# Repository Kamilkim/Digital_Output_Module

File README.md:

# Digital_Output_Module
Digital output to extend number of output of PLC Siemens

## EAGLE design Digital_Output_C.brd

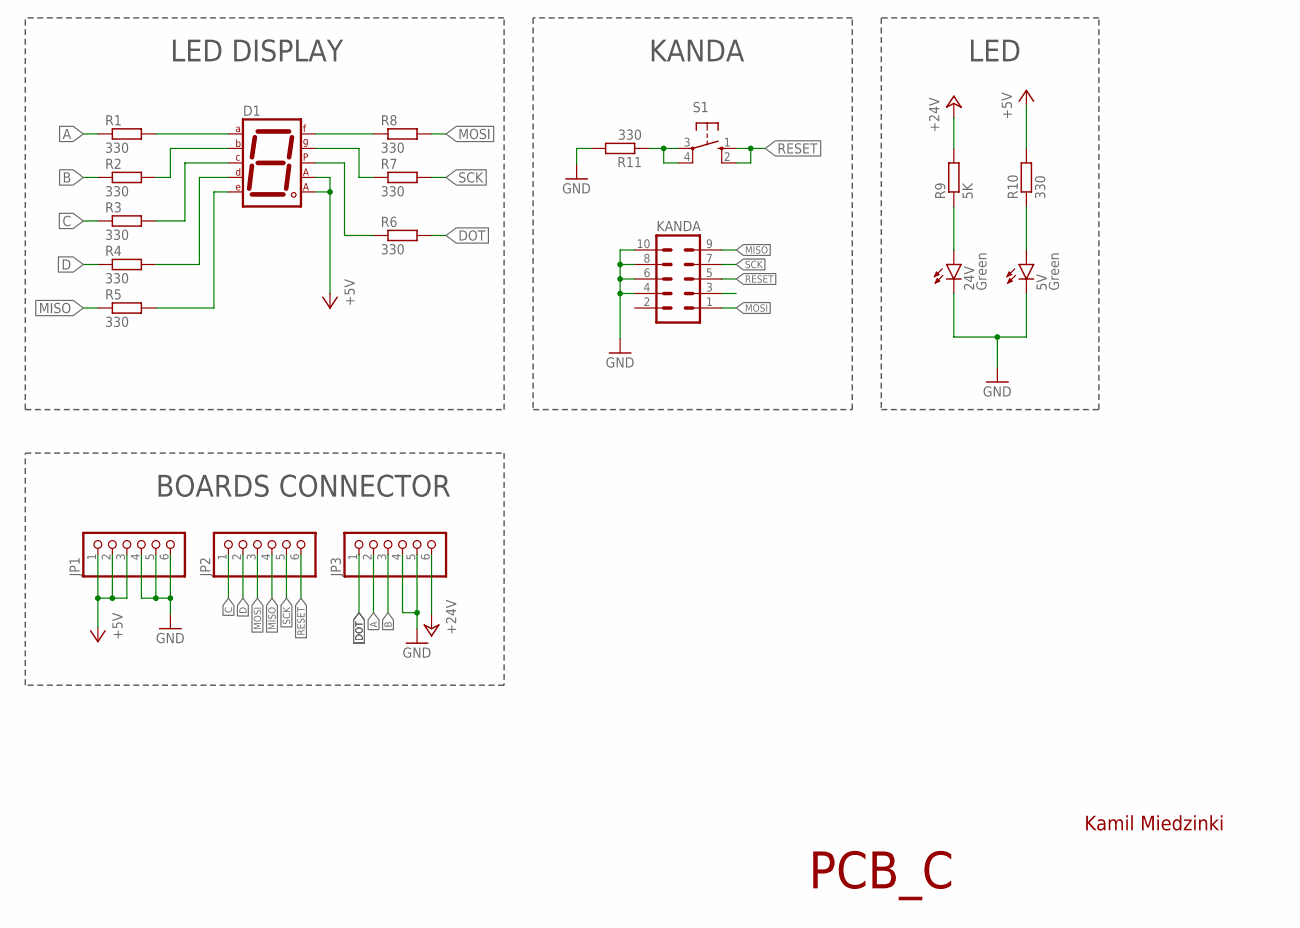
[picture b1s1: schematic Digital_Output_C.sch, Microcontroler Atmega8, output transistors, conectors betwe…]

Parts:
5V, 24V: Green; LED5MM
D1: 7SEG-CA; 7SEG-13
JP1, JP2, JP3: PINHD-1X6"; 1X06H
KANDA: ML10
R1, R2, R3, R4, R5, R6, R7, R8, R11: 330; R0805
R9: 5K; 0207/7
R10: 330; 0207/7
S1: 10-XX; B3F-10XX

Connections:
+5V: D1.3 (CA1), D1.8 (CA2), JP1.1, JP1.2, JP1.3, R10.2
+24V: JP3.6, R9.2
A: JP3.2, R1.1
B: JP3.3, R2.1
C: JP2.1, R3.1
D: JP2.2, R4.1
DOT: JP3.1, R6.2
GND: 5V.K (C), 24V.K (C), JP1.4, JP1.5, JP1.6, JP3.4, JP3.5, KANDA.4, KANDA.6, KANDA.8, KANDA.10, R11.2
MISO: JP2.4, KANDA.9, R5.1
MOSI: JP2.3, KANDA.1, R8.2
unnamed: R11.1, S1.3, S1.4 (P1)
unnamed: D1.7 (A), R1.2
unnamed: D1.6 (B), R2.2
unnamed: D1.4 (C), R3.2
unnamed: D1.2 (D), R4.2
unnamed: D1.1 (E), R5.2
unnamed: D1.9 (F), R8.1
unnamed: D1.10 (G), R7.1
unnamed: D1.5 (DP), R6.1
unnamed: 24V.A, R9.1
unnamed: 5V.A, R10.1
RESET: JP2.6, KANDA.5, S1.1 (S), S1.2 (S1)
SCK: JP2.5, KANDA.7, R7.2

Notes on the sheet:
Kamil Miedzinki
PCB_C
BOARDS CONNECTOR
LED DISPLAY
KANDA
LED

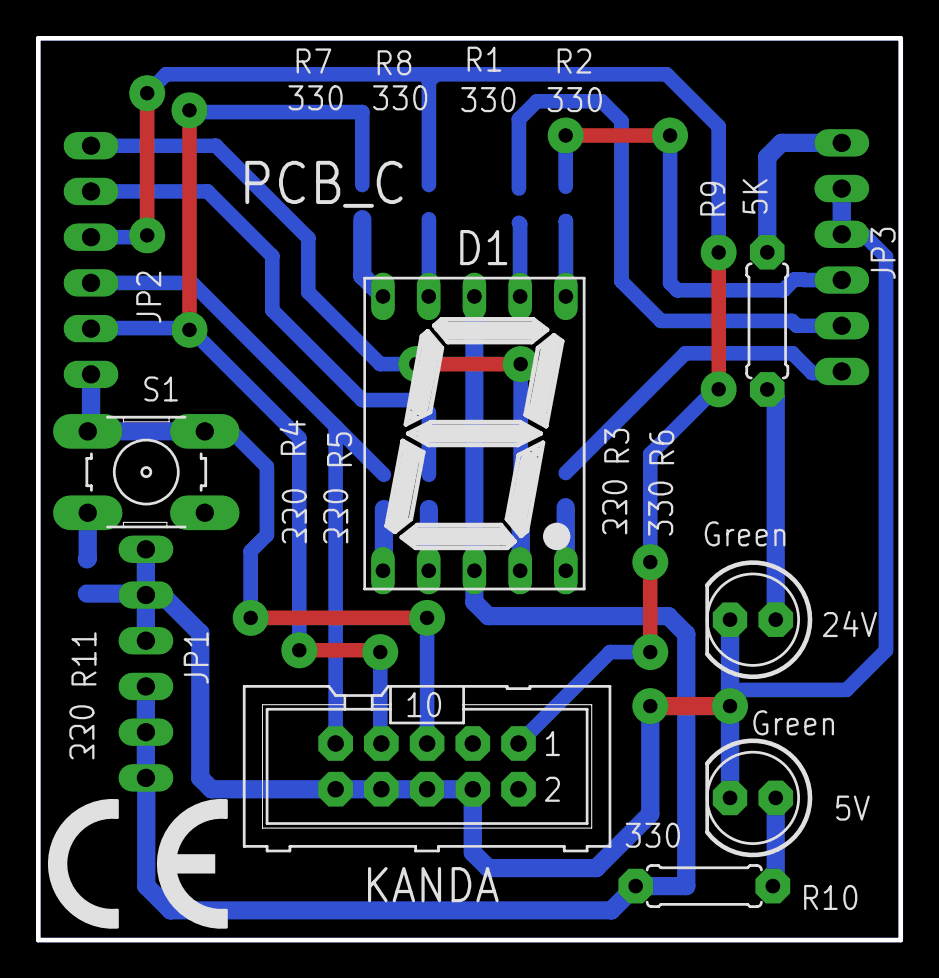
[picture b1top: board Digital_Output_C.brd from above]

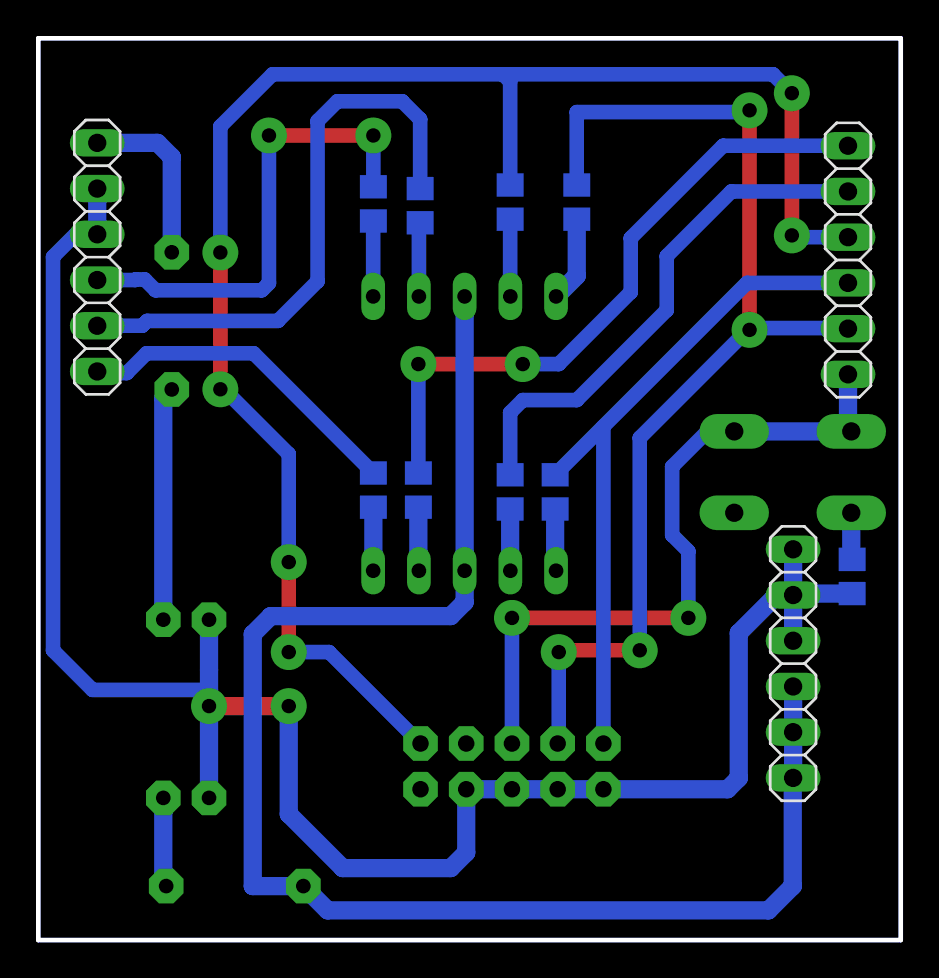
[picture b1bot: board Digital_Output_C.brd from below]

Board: 2 copper layers, 47.9 x 50.1 mm, 21 parts (12 on the bottom side), 23 nets.

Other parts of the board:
U$1: CE_7.3MM
U$2: LOGO

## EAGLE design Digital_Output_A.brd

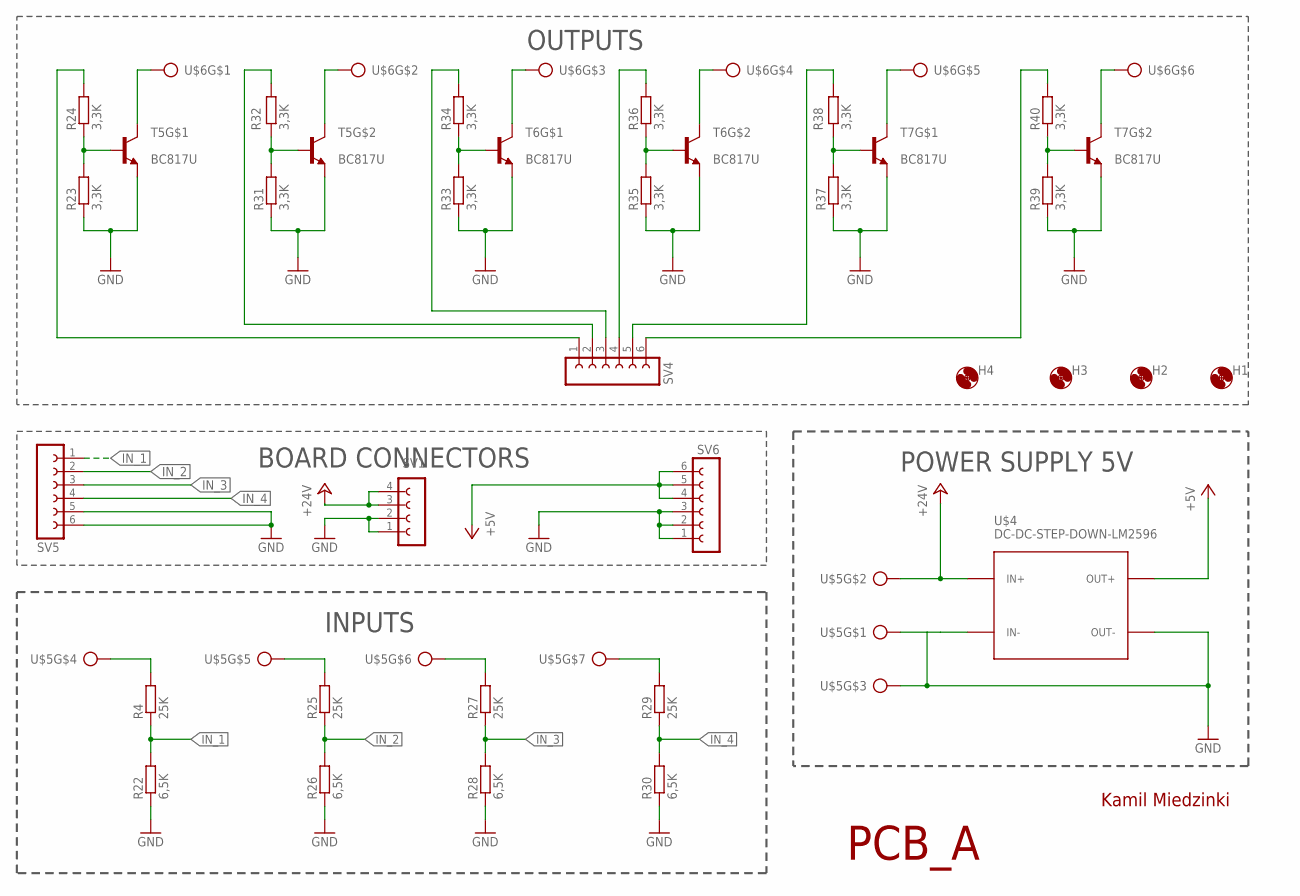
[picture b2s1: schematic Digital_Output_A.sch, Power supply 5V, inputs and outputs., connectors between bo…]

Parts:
H1, H2, H3, H4: MOUNT-HOLE3.3; 3,3
R4, R25, R27, R29: 25K; 0204/7
R22, R26, R28, R30: 6,5K; 0204/7
R23, R24, R31, R32, R33, R34, R35, R36, R37, R38, R39, R40: 3,3K; 0204/7
SV1: FE04-1
SV4, SV5, SV6: FE06-1; FE06
T5, T6, T7: BC817U; INF-SC74
U$4: DC-DC-STEP-DOWN-LM2596
U$5: 24V; MKDSN2,5/7
U$6: MKDSN2,5/6

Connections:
+5V: SV6.4, SV6.5, SV6.6, U$4.OUT+
+24V: SV1.3 (4), SV1.4 (5), U$4.IN+, U$5.2
GND: R22.1, R23.1, R26.1, R28.1, R30.1, R31.1, R33.1, R35.1, R37.1, R39.1, SV1.1 (2), SV1.2 (3), SV5.5, SV5.6, SV6.1, SV6.2, SV6.3, T5.1 (E), T5.4 (E), T6.1 (E), T6.4 (E), T7.1 (E), T7.4 (E), U$4.IN-, U$4.OUT-, U$5.1, U$5.3
IN_1: R4.1, R22.2, SV5.1
IN_2: R25.1, R26.2, SV5.2
IN_3: R27.1, R28.2, SV5.3
IN_4: R29.1, R30.2, SV5.4
unnamed: R4.2, U$5.4
unnamed: R25.2, U$5.5
unnamed: R27.2, U$5.6
unnamed: R29.2, U$5.7
unnamed: T5.6 (C), U$6.1
unnamed: R23.2, R24.1, T5.2 (B)
unnamed: R24.2, SV4.1
unnamed: T5.3 (C), U$6.2
unnamed: R31.2, R32.1, T5.5 (B)
unnamed: R32.2, SV4.2
unnamed: T6.6 (C), U$6.3
unnamed: R33.2, R34.1, T6.2 (B)
unnamed: R34.2, SV4.3
unnamed: T6.3 (C), U$6.4
unnamed: R35.2, R36.1, T6.5 (B)
unnamed: R36.2, SV4.4
unnamed: T7.6 (C), U$6.5
unnamed: R37.2, R38.1, T7.2 (B)
unnamed: R38.2, SV4.5
unnamed: T7.3 (C), U$6.6
unnamed: R39.2, R40.1, T7.5 (B)
unnamed: R40.2, SV4.6

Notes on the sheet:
Kamil Miedzinki
PCB_A
INPUTS
POWER SUPPLY 5V
OUTPUTS
BOARD CONNECTORS

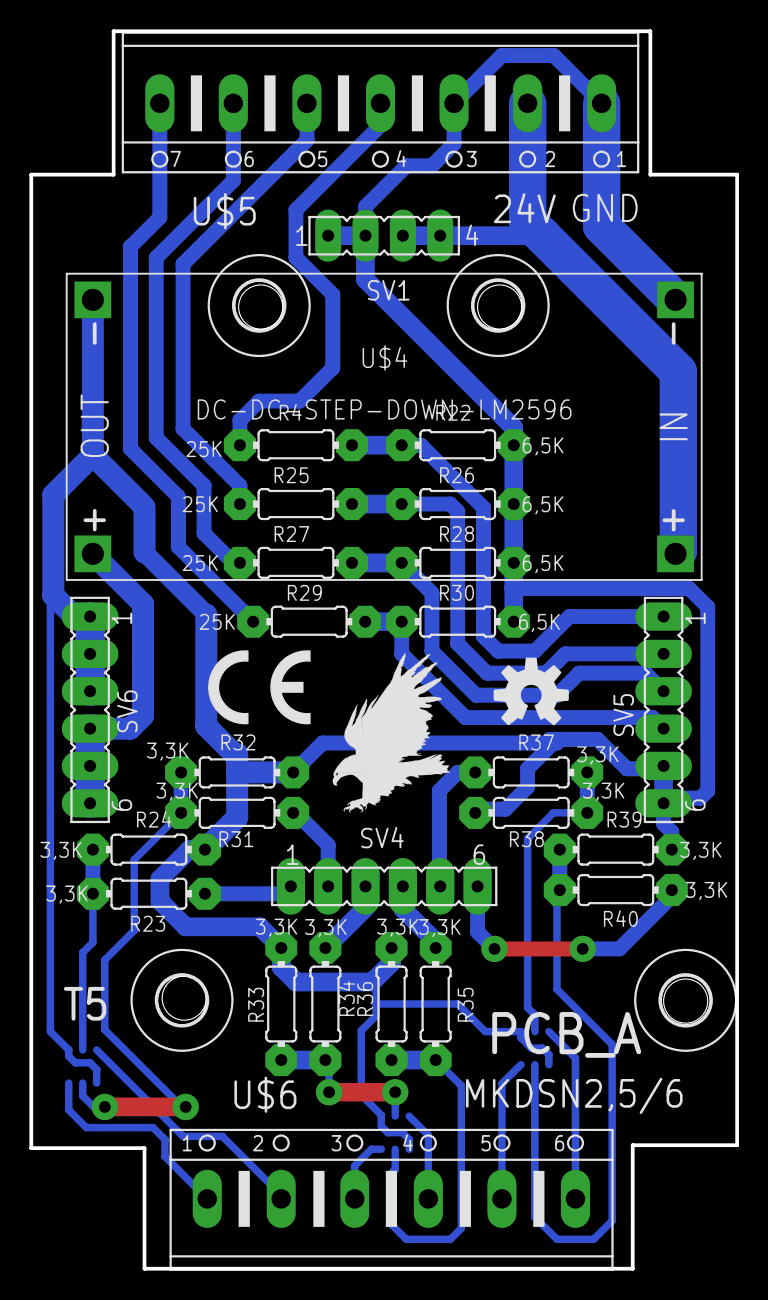
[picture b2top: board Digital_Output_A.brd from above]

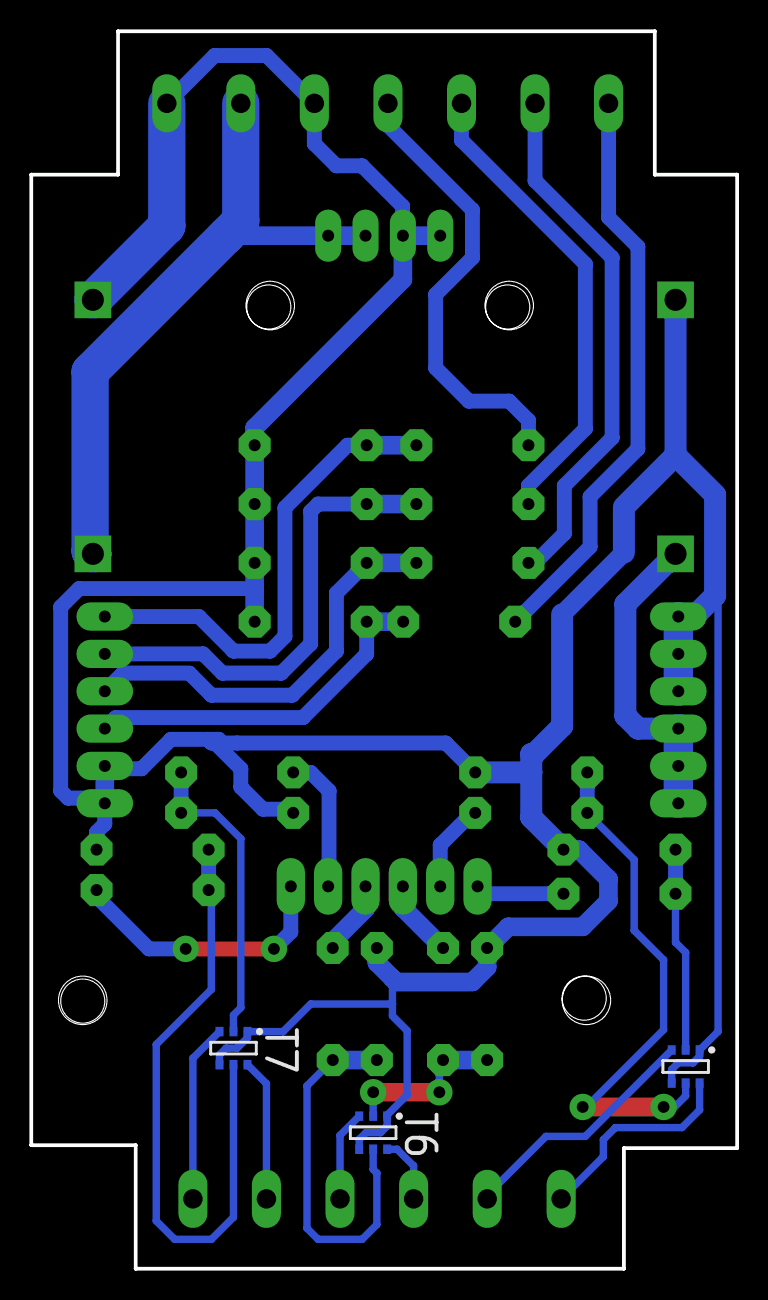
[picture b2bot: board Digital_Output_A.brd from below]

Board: 2 copper layers, 48.0 x 84.2 mm, 37 parts (3 on the bottom side), 29 nets.

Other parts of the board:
U$1: CE_5MM
U$2: EAGLE-PLC-8MM
U$3: OSHW-LOGO-M

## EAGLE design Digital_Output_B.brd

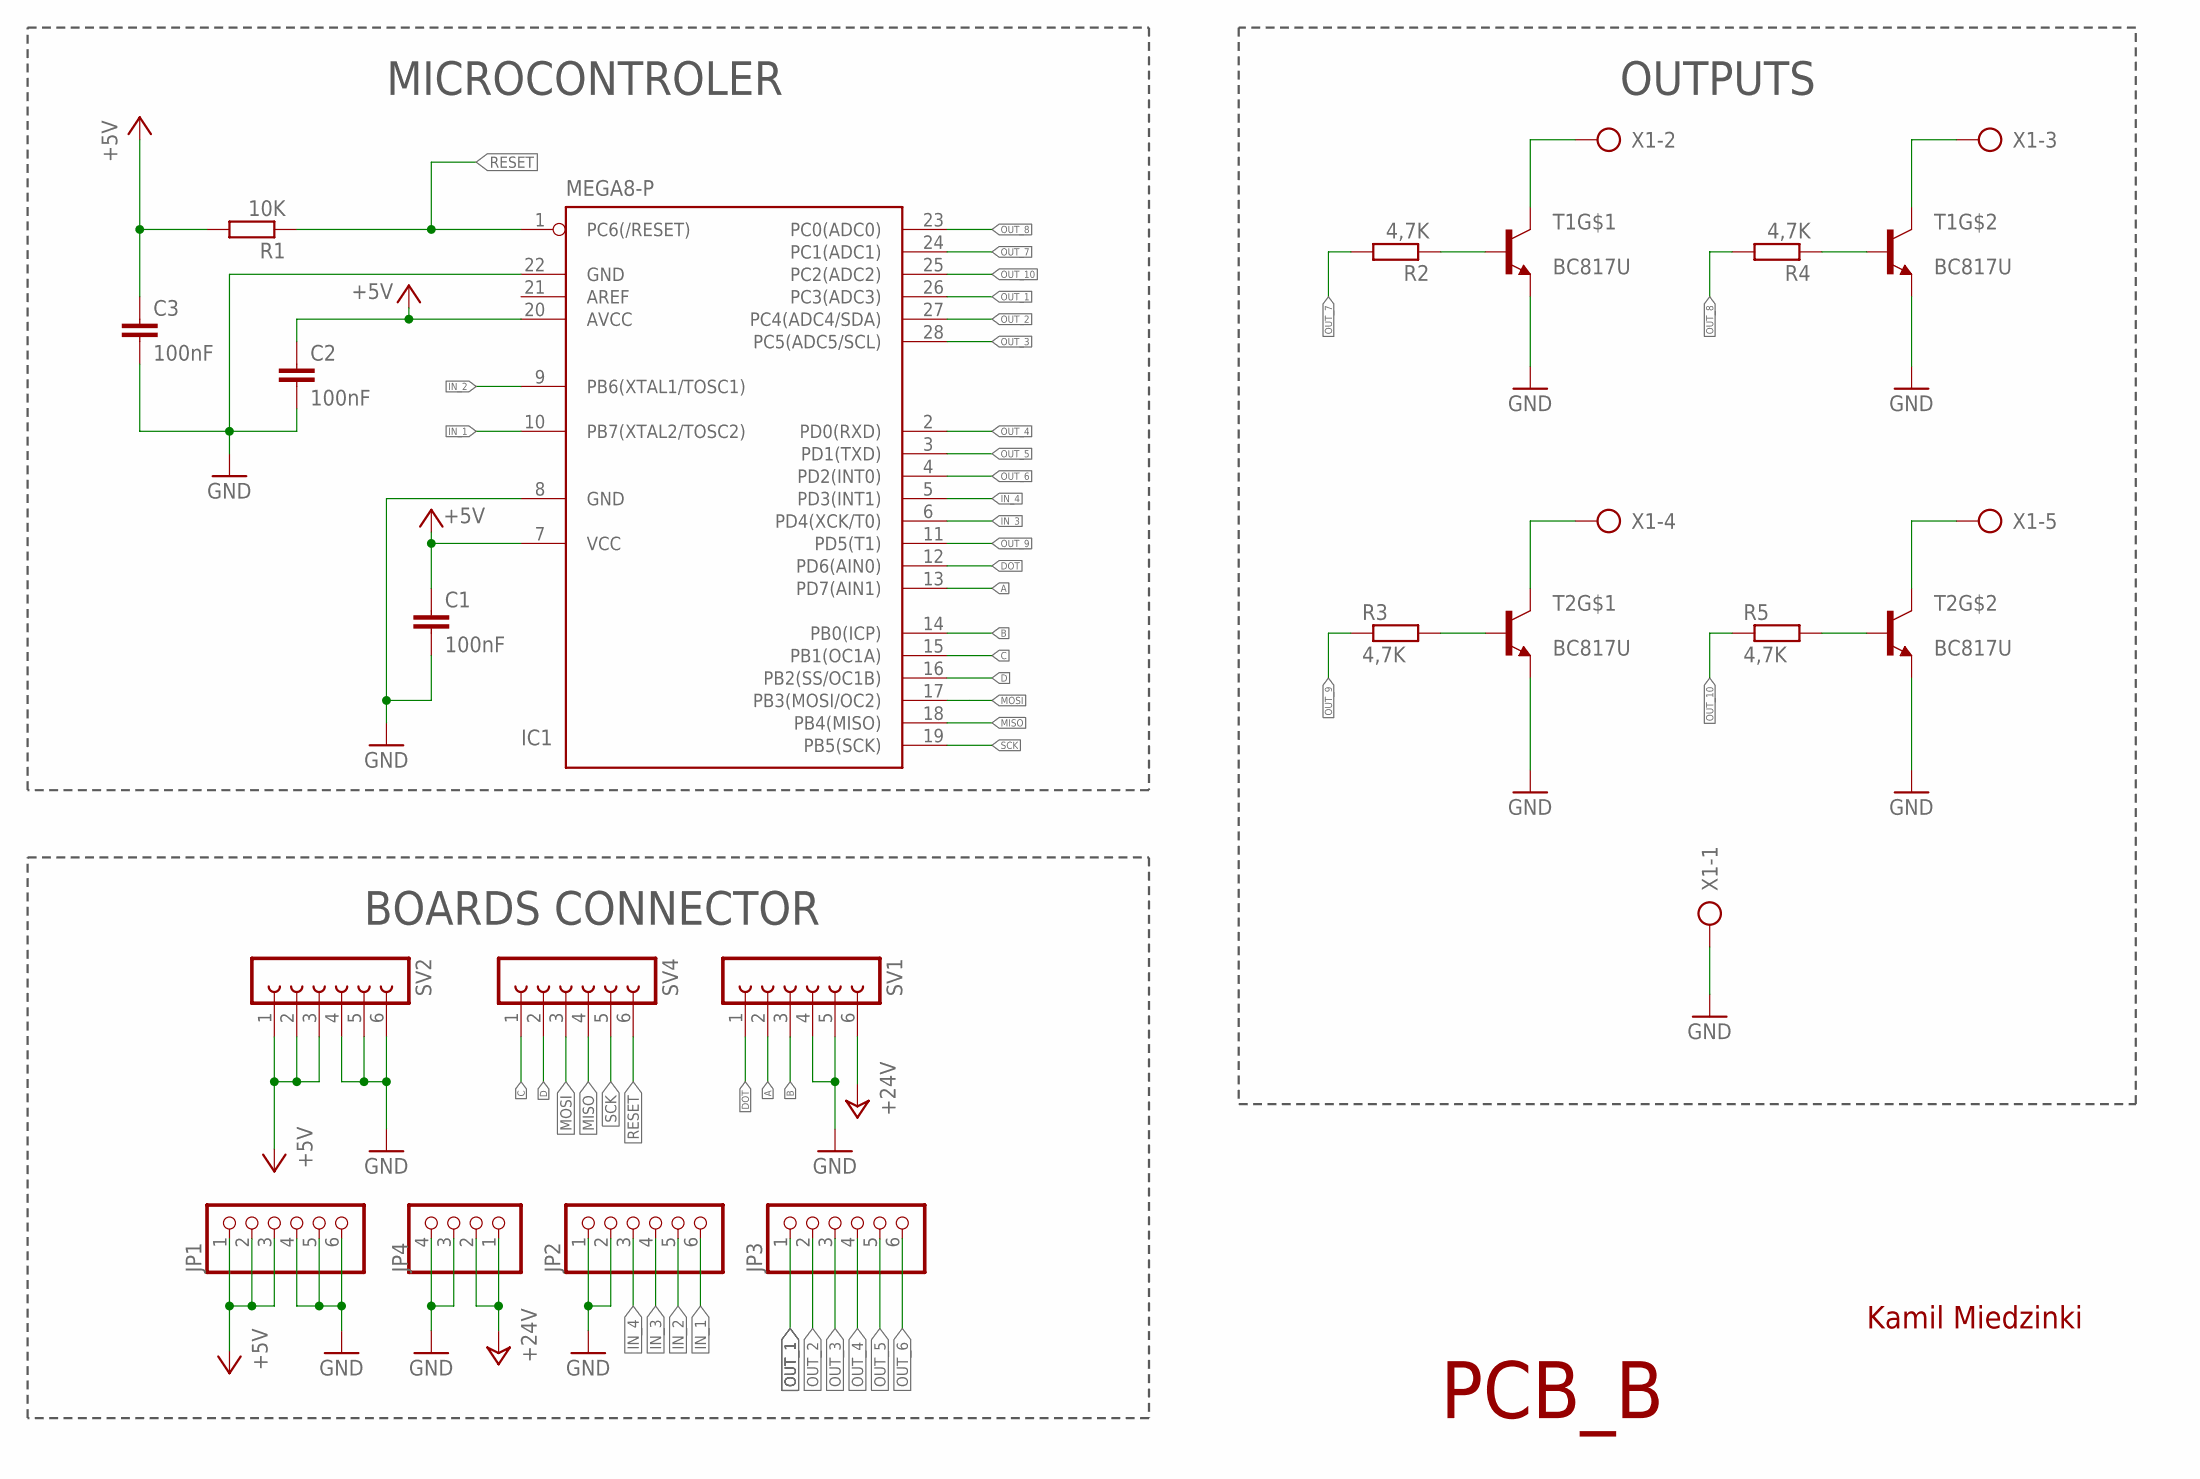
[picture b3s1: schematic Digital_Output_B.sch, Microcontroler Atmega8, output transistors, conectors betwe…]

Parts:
C1, C2, C3: 100nF; C0805K
IC1: MEGA8-P; DIL28-3
JP1, JP2, JP3: PINHD-1X6"; 1X06H
JP4: PINHD-1X41X04H; 1X04H
R1: 10K; R0805
R2, R3, R4, R5: 4,7K; R0805
SV1, SV2, SV4: FE06-1; FE06
T1, T2: BC817U; INF-SC74
X1: MKDS_3/5

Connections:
+5V: C1.1, C2.1, C3.1, IC1.7 (VCC), IC1.20 (AVCC), JP1.1, JP1.2, JP1.3, R1.2, SV2.1, SV2.2, SV2.3
+24V: JP4.1, JP4.2, SV1.6
A: IC1.13 (PD7(AIN1)), SV1.2
B: IC1.14 (PB0(ICP)), SV1.3
C: IC1.15 (PB1(OC1A)), SV4.1
D: IC1.16 (PB2(SS/OC1B)), SV4.2
DOT: IC1.12 (PD6(AIN0)), SV1.1
GND: C1.2, C2.2, C3.2, IC1.8 (GND), IC1.22 (GND), JP1.4, JP1.5, JP1.6, JP2.1, JP2.2, JP4.3, JP4.4, SV1.4, SV1.5, SV2.4, SV2.5, SV2.6, T1.1 (E), T1.4 (E), T2.1 (E), T2.4 (E), X1.1
IN_1: IC1.10 (PB7(XTAL2/TOSC2)), JP2.6
IN_2: IC1.9 (PB6(XTAL1/TOSC1)), JP2.5
IN_3: IC1.6 (PD4(XCK/T0)), JP2.4
IN_4: IC1.5 (PD3(INT1)), JP2.3
MISO: IC1.18 (PB4(MISO)), SV4.4
MOSI: IC1.17 (PB3(MOSI/OC2)), SV4.3
unnamed: T2.6 (C), X1.4
unnamed: T2.3 (C), X1.5
unnamed: T1.3 (C), X1.3
unnamed: T1.6 (C), X1.2
unnamed: R2.1, T1.2 (B)
unnamed: R3.2, T2.2 (B)
unnamed: R4.1, T1.5 (B)
unnamed: R5.2, T2.5 (B)
OUT_1: IC1.26 (PC3(ADC3)), JP3.1
OUT_2: IC1.27 (PC4(ADC4/SDA)), JP3.2
OUT_3: IC1.28 (PC5(ADC5/SCL)), JP3.3
OUT_4: IC1.2 (PD0(RXD)), JP3.4
OUT_5: IC1.3 (PD1(TXD)), JP3.5
OUT_6: IC1.4 (PD2(INT0)), JP3.6
OUT_7: IC1.24 (PC1(ADC1)), R2.2
OUT_8: IC1.23 (PC0(ADC0)), R4.2
OUT_9: IC1.11 (PD5(T1)), R3.1
OUT_10: IC1.25 (PC2(ADC2)), R5.1
RESET: IC1.1 (PC6(/RESET)), R1.1, SV4.6
SCK: IC1.19 (PB5(SCK)), SV4.5

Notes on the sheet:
Kamil Miedzinki
PCB_B
MICROCONTROLER
OUTPUTS
BOARDS CONNECTOR

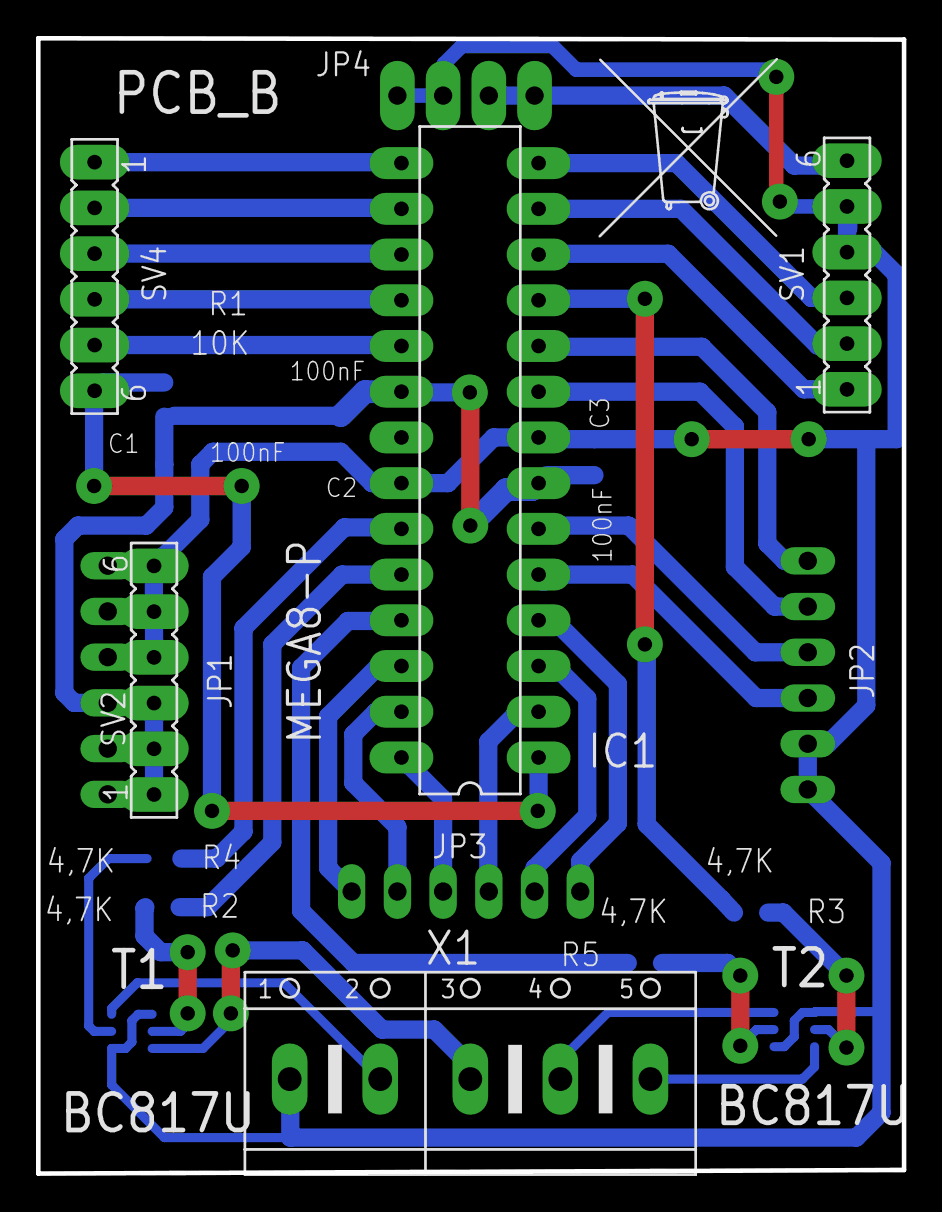
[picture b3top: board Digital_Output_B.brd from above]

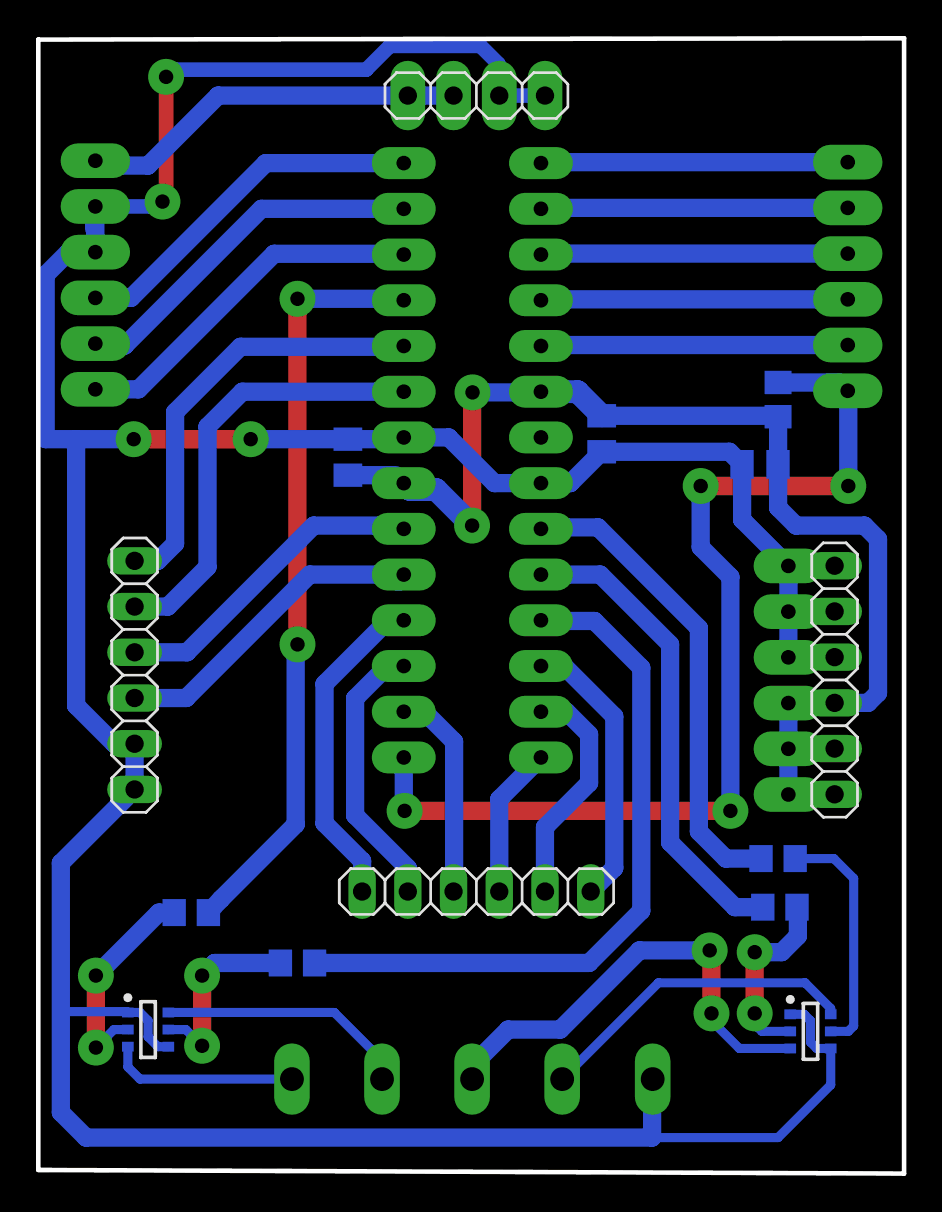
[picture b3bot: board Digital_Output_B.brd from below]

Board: 2 copper layers, 48.1 x 63.1 mm, 21 parts (14 on the bottom side), 34 nets.

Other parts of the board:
U$1: LOGO
U$2: TONNE_10.00

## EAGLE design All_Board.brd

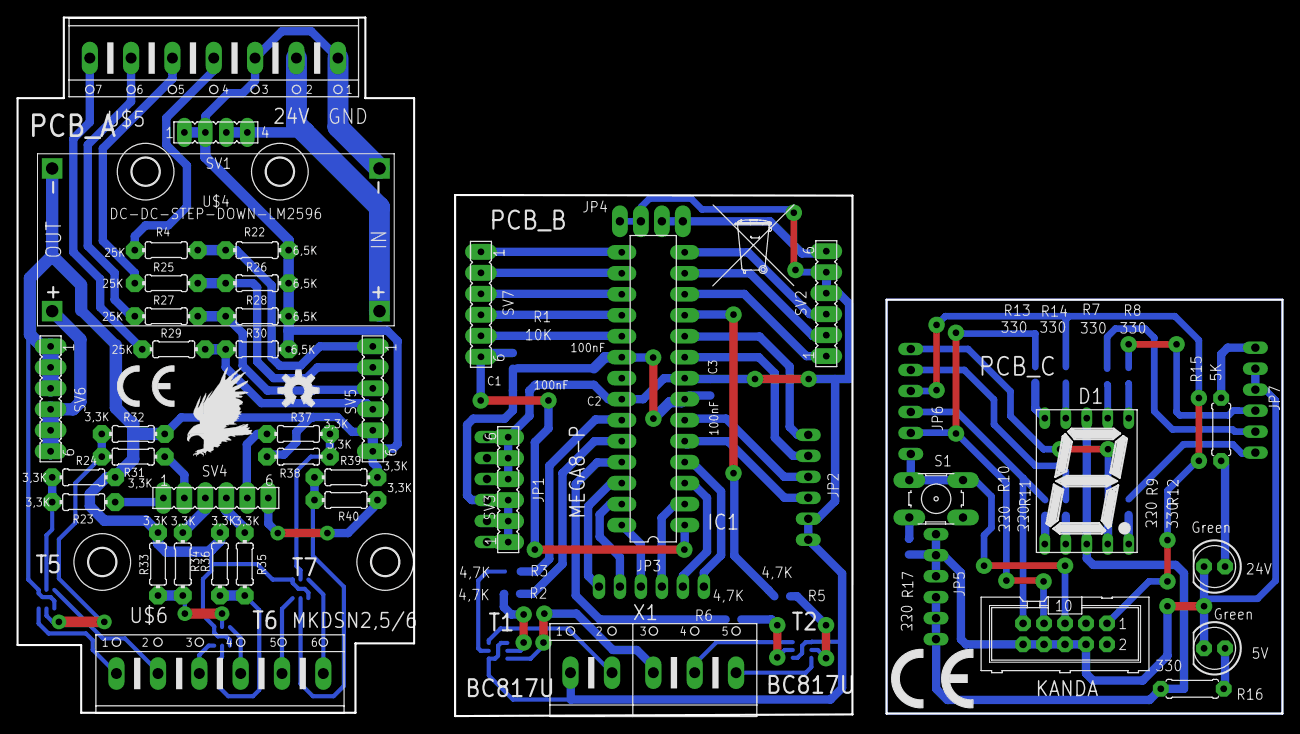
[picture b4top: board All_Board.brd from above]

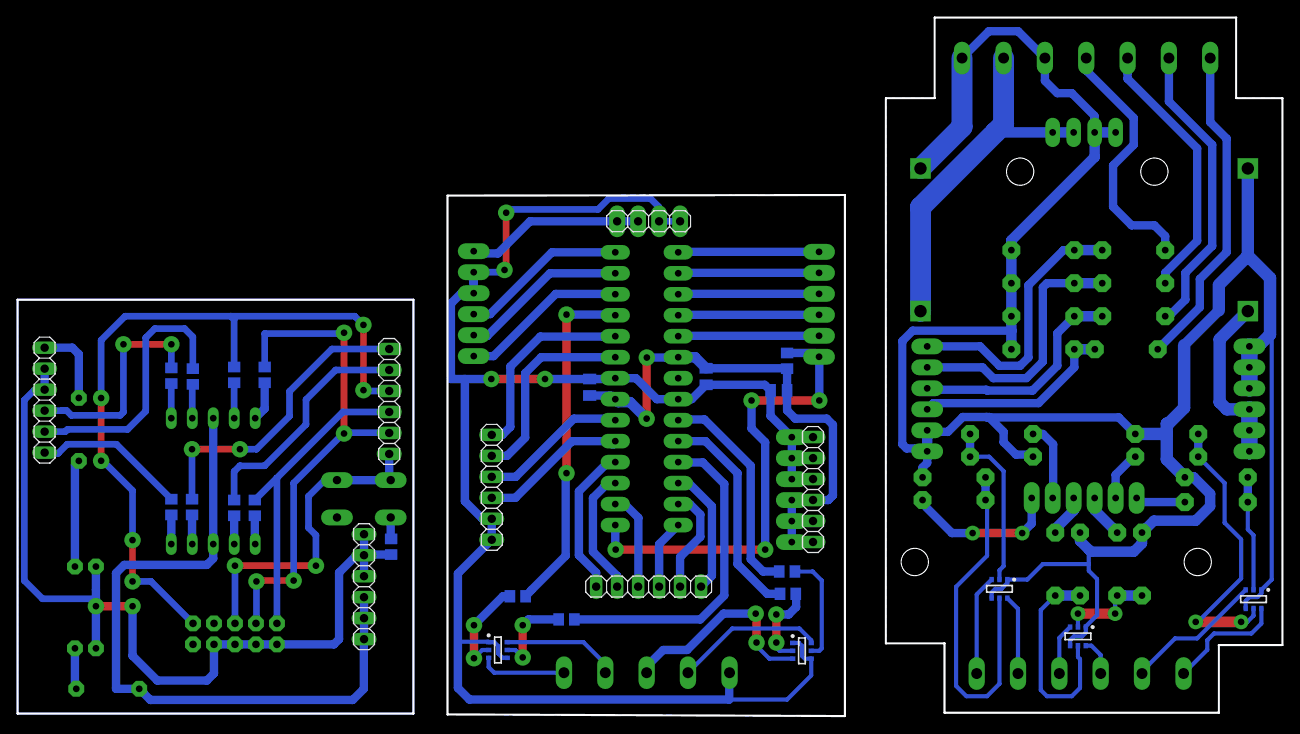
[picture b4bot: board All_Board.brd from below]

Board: 2 copper layers, 153.1 x 84.5 mm, 79 parts (29 on the bottom side), 86 nets.

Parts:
5V, 24V: Green; LED5MM
C1, C2, C3: 100nF; C0805K
D1: 7SEG-13
H1, H2, H3, H4: MOUNT-HOLE3.3; 3,3
IC1: MEGA8-P; DIL28-3
JP1, JP2, JP3, JP5, JP6, JP7: 1X06H
JP4: 1X04H
KANDA: ML10
R1: 10K; R0805
R2, R3, R5, R6: 4,7K; R0805
R4, R25, R27, R29: 25K; 0204/7
R7, R8, R9, R10, R11, R12, R13, R14, R17: 330; R0805
R15: 5K; 0207/7
R16: 330; 0207/7
R22, R26, R28, R30: 6,5K; 0204/7
R23, R24, R31, R32, R33, R34, R35, R36, R37, R38, R39, R40: 3,3K; 0204/7
S1: B3F-10XX
SV1: FE04-1
SV2, SV3, SV4, SV5, SV6, SV7: FE06
T1, T2, T5, T6, T7: BC817U; INF-SC74
U$1: CE_5MM
U$2: EAGLE-PLC-8MM
U$3: OSHW-LOGO-M
U$4: DC-DC-STEP-DOWN-LM2596
U$5: 24V; MKDSN2,5/7
U$6: MKDSN2,5/6
U$7, U$10: LOGO
U$8: TONNE_10.00
U$9: CE_7.3MM
X1: MKDS_3/5

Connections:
+5V: SV6.4, SV6.5, SV6.6, U$4.OUT+
+5V1: C1.1, C2.1, C3.1, IC1.7, IC1.20, JP1.1, JP1.2, JP1.3, R1.2, SV3.1, SV3.2, SV3.3
+5V2: D1.3, D1.8, JP5.1, JP5.2, JP5.3, R16.2
+24V: SV1.3, SV1.4, U$4.IN+, U$5.2
+24V1: JP4.1, JP4.2, SV2.6
+24V2: JP7.6, R15.2
A: IC1.13, SV2.2
A1: JP7.2, R7.1
B: IC1.14, SV2.3
B1: JP7.3, R8.1
C: IC1.15, SV7.1
C1: JP6.1, R9.1
D: IC1.16, SV7.2
D1: JP6.2, R10.1
DOT: IC1.12, SV2.1
DOT1: JP7.1, R12.2
GND: R22.1, R23.1, R26.1, R28.1, R30.1, R31.1, R33.1, R35.1, R37.1, R39.1, SV1.1, SV1.2, SV5.5, SV5.6, SV6.1, SV6.2, SV6.3, T5.1, T5.4, T6.1, T6.4, T7.1, T7.4, U$4.IN-, U$4.OUT-, U$5.1, U$5.3
GND1: C1.2, C2.2, C3.2, IC1.8, IC1.22, JP1.4, JP1.5, JP1.6, JP2.1, JP2.2, JP4.3, JP4.4, SV2.4, SV2.5, SV3.4, SV3.5, SV3.6, T1.1, T1.4, T2.1, T2.4, X1.1
GND2: 5V.K, 24V.K, JP5.4, JP5.5, JP5.6, JP7.4, JP7.5, KANDA.4, KANDA.6, KANDA.8, KANDA.10, R17.2
IN_1: R4.1, R22.2, SV5.1
IN_2: R25.1, R26.2, SV5.2
IN_3: R27.1, R28.2, SV5.3
IN_4: R29.1, R30.2, SV5.4
IN_5: IC1.10, JP2.6
IN_6: IC1.9, JP2.5
IN_7: IC1.6, JP2.4
IN_8: IC1.5, JP2.3
MISO: IC1.18, SV7.4
MISO1: JP6.4, KANDA.9, R11.1
MOSI: IC1.17, SV7.3
MOSI1: JP6.3, KANDA.1, R14.2
unnamed: T2.6, X1.4
unnamed: T2.3, X1.5
unnamed: T1.3, X1.3
unnamed: T1.6, X1.2
unnamed: R2.1, T1.2
unnamed: R5.2, T2.2
unnamed: R3.1, T1.5
unnamed: R6.2, T2.5
unnamed: R17.1, S1.3, S1.4
unnamed: D1.7, R7.2
unnamed: D1.6, R8.2
unnamed: D1.4, R9.2
unnamed: D1.2, R10.2
unnamed: D1.1, R11.2
unnamed: D1.9, R14.1
unnamed: D1.10, R13.1
unnamed: D1.5, R12.1
unnamed: 24V.A, R15.1
unnamed: 5V.A, R16.1
unnamed: R4.2, U$5.4
unnamed: R25.2, U$5.5
unnamed: R27.2, U$5.6
unnamed: R29.2, U$5.7
unnamed: T5.6, U$6.1
unnamed: R23.2, R24.1, T5.2
unnamed: R24.2, SV4.1
unnamed: T5.3, U$6.2
unnamed: R31.2, R32.1, T5.5
unnamed: R32.2, SV4.2
unnamed: T6.6, U$6.3
unnamed: R33.2, R34.1, T6.2
unnamed: R34.2, SV4.3
unnamed: T6.3, U$6.4
unnamed: R35.2, R36.1, T6.5
unnamed: R36.2, SV4.4
unnamed: T7.6, U$6.5
unnamed: R37.2, R38.1, T7.2
unnamed: R38.2, SV4.5
unnamed: T7.3, U$6.6
unnamed: R39.2, R40.1, T7.5
unnamed: R40.2, SV4.6
OUT_1: IC1.26, JP3.1
OUT_2: IC1.27, JP3.2
OUT_3: IC1.28, JP3.3
OUT_4: IC1.2, JP3.4
OUT_5: IC1.3, JP3.5
OUT_6: IC1.4, JP3.6
OUT_7: IC1.24, R2.2
OUT_8: IC1.23, R3.2
OUT_9: IC1.11, R5.1
OUT_10: IC1.25, R6.1
RESET: IC1.1, R1.1, SV7.6
RESET1: JP6.6, KANDA.5, S1.1, S1.2
SCK: IC1.19, SV7.5
SCK1: JP6.5, KANDA.7, R13.2

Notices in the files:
parts and their libraries:
diy-modules: Released under the Creative Commons Attribution 4.0 International License: http://creativecommons.org/licenses/by/4.0
Particle-Devices: Licensing: Designed by Particle.
